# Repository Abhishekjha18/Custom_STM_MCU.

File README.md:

# **Custom Microcontroller Board with Multi-Shield Support**  

## Overview  
This project features a **custom-designed microcontroller board** with optimized **hardware interfaces and firmware**, developed using **CubeMX**. It supports **four interchangeable shields**, allowing multiple functionalities to be deployed simultaneously.  

## Features  
- **Custom PCB Design** – Developed using **KiCad** (schematics & layout available in this repository).  
- **Optimized Firmware** – Configured and fine-tuned with **CubeMX** for efficient performance.  
- **Multi-Shield Support** – Simultaneously deploy up to **four shields** with distinct functionalities.  
- **Scalable & Modular** – Easily adaptable for various embedded applications.  

## Access KiCad Files  
All **schematic and PCB design files** are available in the **KiCad_Files** directory of this repository. Clone or download them to modify or manufacture your custom board.  

1. Open **KiCad** and load the project files from the **KiCad_Files** folder.  
2. Use **CubeMX** to configure or modify firmware as needed.  
3. Flash the firmware to the microcontroller and test with your desired shields.

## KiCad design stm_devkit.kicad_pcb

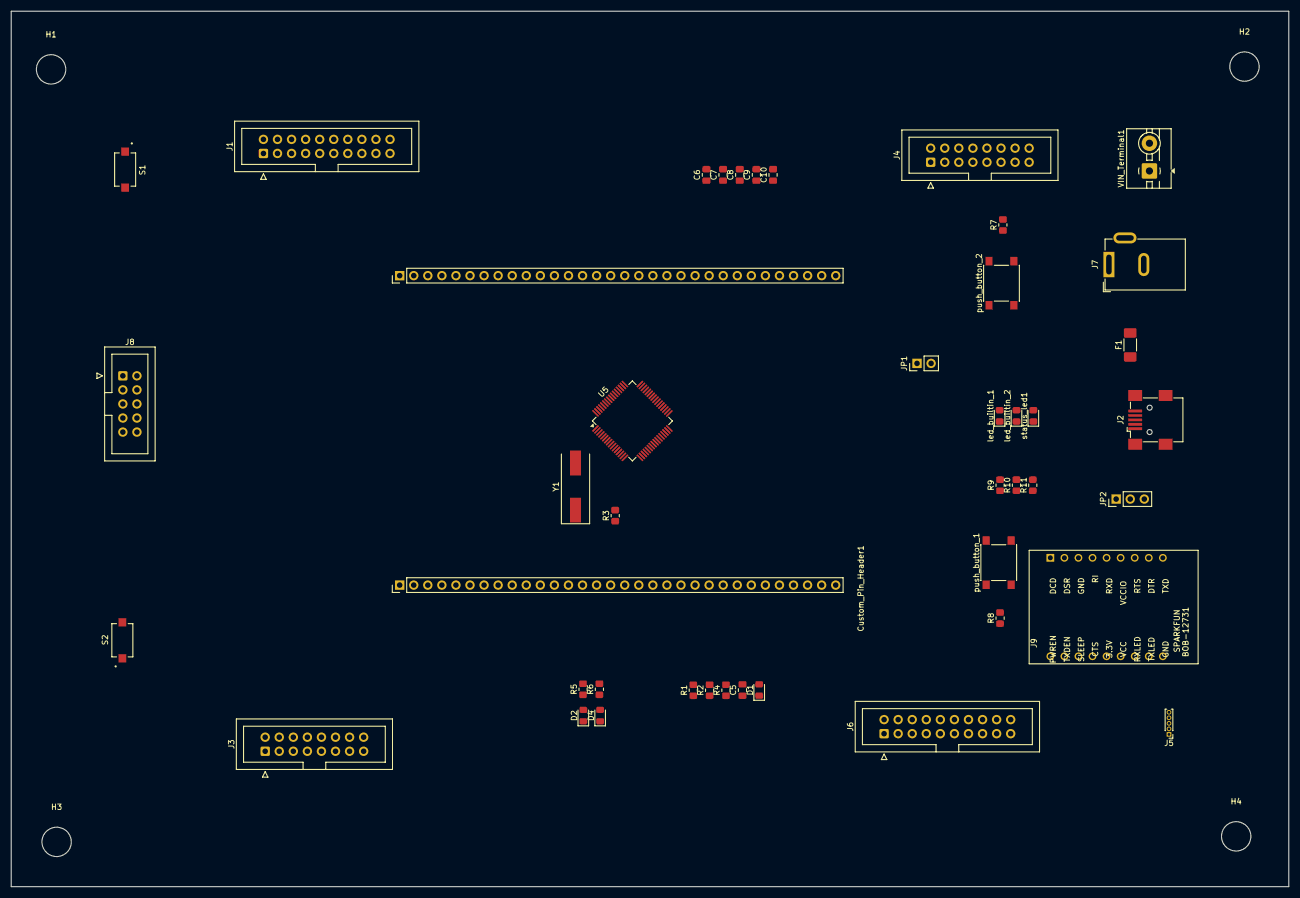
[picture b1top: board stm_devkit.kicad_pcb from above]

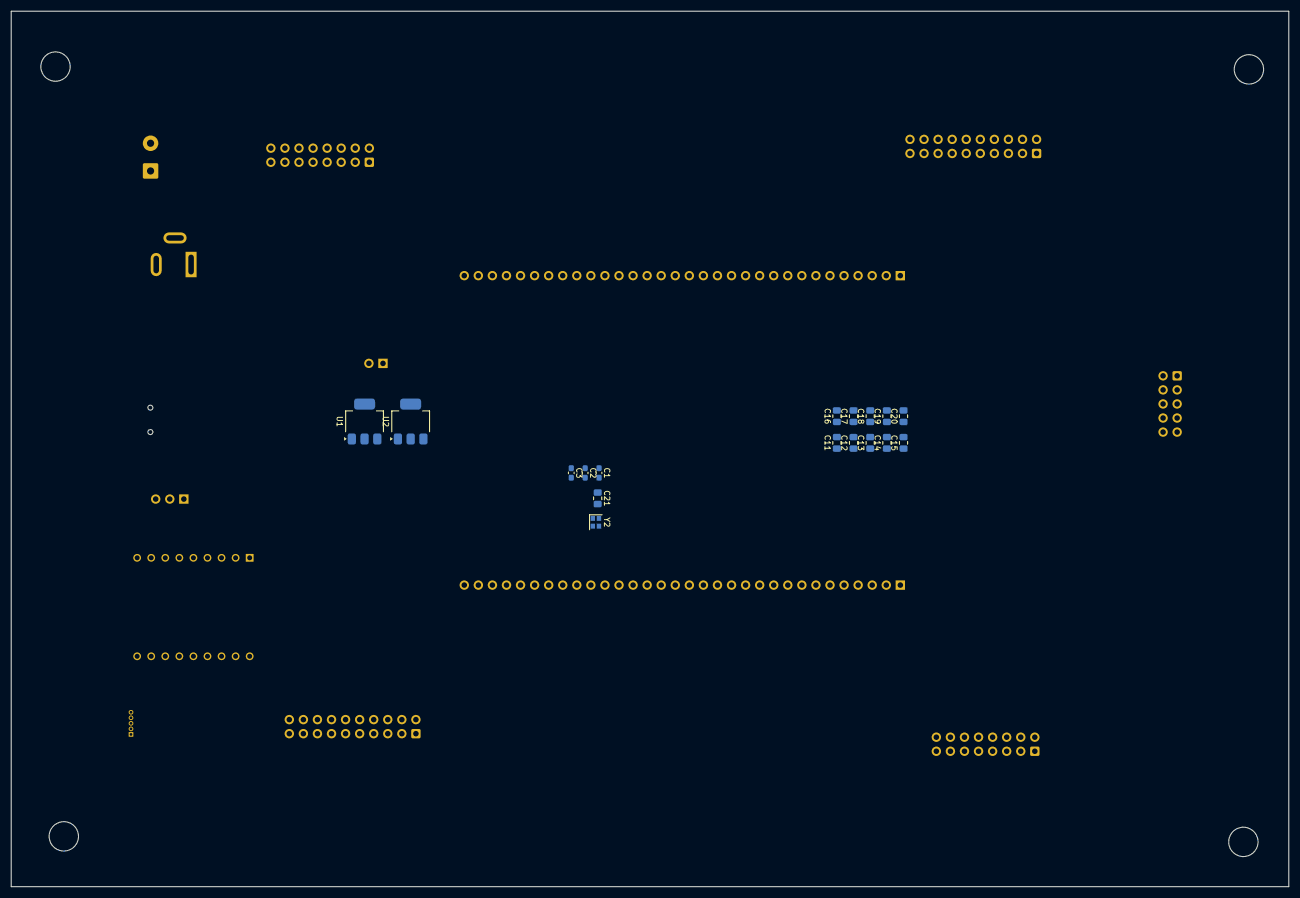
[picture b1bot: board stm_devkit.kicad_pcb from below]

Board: 2 copper layers, 230.7 x 158.1 mm, 64 parts (17 on the bottom side), 74 nets, no tracks yet.

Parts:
C1, C2: 22pF; C_0603_1608Metric_Pad1.08x0.95mm_HandSolder
C3: 10pF; C_0603_1608Metric_Pad1.08x0.95mm_HandSolder
C5: 0.01u; C_0805_2012Metric_Pad1.18x1.45mm_HandSolder
C6, C8, C9: 10uF, 25V; C_0805_2012Metric_Pad1.18x1.45mm_HandSolder
C7, C10: 1uF; C_0805_2012Metric_Pad1.18x1.45mm_HandSolder
C11, C13, C16, C19: 10uF; C_0805_2012Metric_Pad1.18x1.45mm_HandSolder
C12, C14, C15, C17, C18, C20: 0.1uF; C_0805_2012Metric_Pad1.18x1.45mm_HandSolder
C21: C_Trim; C_0805_2012Metric_Pad1.18x1.45mm_HandSolder
Custom_Pin_Header1: 64_pin_header
D1: 1N4148; D_0805_2012Metric_Pad1.15x1.40mm_HandSolder
D2: PWR_LED; LED_0805_2012Metric_Pad1.15x1.40mm_HandSolder
D4: D; D_0805_2012Metric_Pad1.15x1.40mm_HandSolder
F1: Polyfuse; C_1808_4520Metric_Pad1.72x2.30mm_HandSolder
H1, H2, H3, H4: MountingHole; MountingHole_5.3mm_M5
J1, J6: Conn_02x10_Odd_Even; IDC-Header_2x10_P2.54mm_Vertical
J2: USB_B_Mini; USB_Mini-B_Wuerth_65100516121_Horizontal
J3, J4: Conn_02x08_Odd_Even; IDC-Header_2x08_P2.54mm_Vertical
J5: Conn_01x05_Pin; PinHeader_1x05_P1.00mm_Vertical
J7: Barrel_Jack_Switch; BarrelJack_GCT_DCJ200-10-A_Horizontal
J8: Conn_02x05_Odd_Even; IDC-Header_2x05_P2.54mm_Vertical
J9: BOB-12731
JP1: Bypass; PinHeader_1x02_P2.54mm_Vertical
JP2: Jumper_3_Open; PinHeader_1x03_P2.54mm_Vertical
R1, R4, R7, R8: 10k; R_0805_2012Metric_Pad1.20x1.40mm_HandSolder
R2: 100K; R_0805_2012Metric_Pad1.20x1.40mm_HandSolder
R3: 1K; R_0805_2012Metric_Pad1.20x1.40mm_HandSolder
R5, R9, R10, R11: 1k; R_0805_2012Metric_Pad1.20x1.40mm_HandSolder
R6: 0; R_0805_2012Metric_Pad1.20x1.40mm_HandSolder
S1, S2: TS10-63-26-BE-250-SMT-TR; SW_TS10-63-26-BE-250-SMT-TR
U1: AMS1117-5.0; SOT-223-3_TabPin2
U2: AMS1117-3.3; SOT-223-3_TabPin2
U5: STM32G070RBTx; LQFP-64_10x10mm_P0.5mm
VIN_Terminal1: Screw_Terminal_01x02; TerminalBlock_MaiXu_MX126-5.0-02P_1x02_P5.00mm
Y1: 8MHz; Crystal_SMD_HC49-SD
Y2: 32.768 kHz; Crystal_SMD_2016-4Pin_2.0x1.6mm
led_builtin_1, led_builtin_2: LED; LED_0805_2012Metric_Pad1.15x1.40mm_HandSolder
push_button_1, push_button_2: SW_Push; SW_SPST_PTS645
status_led1: LED; LED_0805_2012Metric_Pad1.15x1.40mm_HandSolder

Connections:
+3.3V: C15.1, C18.1, Custom_Pin_Header1.8 (VDD), D1.1 (K), J1.13, J1.15, J5.1, J6.13, J6.15, J8.7, J8.8, J9.5 (3V3), R1.1, R4.2, R6.2, R7.1, R8.1, U5.8 (VDD)
+5V: C8.1, C13.1, C14.2, C16.1, C17.2, Custom_Pin_Header1.6 (VBAT), J1.1, J3.1, J3.3, J4.1, J4.2, J4.3, J6.1, JP1.1 (A), JP2.1 (A), U1.3 (VI), U5.6 (VBAT)
GND: C1.1, C2.1, C3.1, C5.2, C6.2, C7.2, C8.2, C9.2, C10.2, C11.2, C12.2, C13.2, C14.1, C15.2, C16.2, C17.1, C18.2, C19.2, C20.2, C21.1, Custom_Pin_Header1.7 (VREF+), Custom_Pin_Header1.9 (VSS), D2.2 (A), D4.2 (A), J1.3, J1.17, J1.19, J1.20, J2.5 (GND), J2.6 (Shield), J3.13, J3.15, J4.13, J4.15, J4.16, J5.4, J6.3, J6.17, J6.19, J6.20, J7.1, J7.3, J8.3, J8.4, J9.9 (GND), R2.2, S2.1, U1.1 (GND), U2.1 (GND), U5.7 (VREF+), U5.9 (VSS), VIN_Terminal1.2, led_builtin_1.1 (K), led_builtin_2.1 (K), push_button_1.2, push_button_2.2, status_led1.1 (K)
I2C1_A_SCL: Custom_Pin_Header1.60 (PB6), J1.14, U5.60 (PB6)
I2C1_A_SDA: Custom_Pin_Header1.61 (PB7), J1.16, U5.61 (PB7)
I2C2_A_SCL: Custom_Pin_Header1.43 (PA11), J3.14, U5.43 (PA9/PA11)
I2C2_A_SDA: Custom_Pin_Header1.44 (PA12), J3.16, U5.44 (PA10/PA12)
I2C2_B_SCL: Custom_Pin_Header1.33 (PB13), J6.14, U5.33 (PB13)
I2C2_B_SDA: Custom_Pin_Header1.34 (PB14), J6.16, U5.34 (PB14)
LED_1: Custom_Pin_Header1.35 (PB15), R9.1, U5.35 (PB15)
LED_2: Custom_Pin_Header1.40 (PD8), R10.1, U5.40 (PD8)
NRST: C5.1, Custom_Pin_Header1.12 (NRST), D1.2 (A), J8.1, R1.2, S2.2, U5.12 (NRST)
unnamed: C2.2, R3.2, Y1.1
unnamed: D2.1 (K), R5.2
unnamed: R4.1, S1.2
unnamed: C6.1, C7.1, R5.1, R6.1, U2.3 (VI)
unnamed: F1.2, J7.2, VIN_Terminal1.1
unnamed: R10.2, led_builtin_1.2 (A)
unnamed: R9.2, led_builtin_2.2 (A)
unnamed: R11.2, status_led1.2 (A)
OSC32_IN: C3.2, Custom_Pin_Header1.4 (PC14-OSC32_IN), U5.4 (PC14), Y2.2
OSC32_OUT: C21.2, Custom_Pin_Header1.5 (PC15-OSC32_OUT), U5.5 (PC15), Y2.1
OSC_IN: C1.2, U5.10 (PF0), Y1.2
OSC_OUT: R3.1, U5.11 (PF1)
PA8: Custom_Pin_Header1.36 (PA8), J4.11, U5.36 (PA8)
PC0: Custom_Pin_Header1.13 (PC0), J6.9, U5.13 (PC0)
PC1: Custom_Pin_Header1.14 (PC1), J6.11, U5.14 (PC1)
PC2: Custom_Pin_Header1.15 (PC2), J4.4, U5.15 (PC2)
PC3: Custom_Pin_Header1.16 (PC3), J4.6, U5.16 (PC3)
PC6: Custom_Pin_Header1.39 (PC7), J3.9, U5.38 (PC6)
PC7: Custom_Pin_Header1.38 (PC6), J3.11, U5.39 (PC7)
PC8: Custom_Pin_Header1.49 (PC9), J1.9, U5.48 (PC8)
PC9: Custom_Pin_Header1.48 (PC8), J1.11, U5.49 (PC9)
PD2: Custom_Pin_Header1.56 (PD6), J4.8, U5.52 (PD2)
PD5: Custom_Pin_Header1.53 (PD3), J4.10, U5.55 (PD5)
PD6: Custom_Pin_Header1.52 (PD2), J4.12, U5.56 (PD6)
PD9: Custom_Pin_Header1.41 (PD9), J4.14, U5.41 (PD9)
PUSH_DEF_1: Custom_Pin_Header1.30 (PB10), R8.2, U5.30 (PB10), push_button_1.1
PUSH_DEF_2: Custom_Pin_Header1.2 (PC12), R7.2, U5.2 (PC12), push_button_2.1
SPI1_A_MISO: Custom_Pin_Header1.24 (PA7), J6.6, U5.24 (PA7)
SPI1_A_MOSI: Custom_Pin_Header1.23 (PA6), J6.4, U5.23 (PA6)
SPI1_A_NSS: Custom_Pin_Header1.21 (PA4), J6.8, U5.21 (PA4)
SPI1_A_SCK: Custom_Pin_Header1.22 (PA5), J6.2, U5.22 (PA5)
SPI1_B_MISO: Custom_Pin_Header1.59 (PB5), J3.6, U5.59 (PB5)
SPI1_B_MOSI: Custom_Pin_Header1.58 (PB4), J3.4, U5.58 (PB4)
SPI1_B_NSS: Custom_Pin_Header1.47 (PA15), J3.8, U5.47 (PA15)
SPI1_B_SCK: Custom_Pin_Header1.57 (PB3), J3.2, U5.57 (PB3)
SPI2_B_MISO: Custom_Pin_Header1.55 (PD5), J1.6, U5.53 (PD3)
SPI2_B_MOSI: Custom_Pin_Header1.54 (PD4), J1.4, U5.54 (PD4)
SPI2_B_NSS: Custom_Pin_Header1.50 (PD0), J1.8, U5.50 (PD0)
SPI2_B_SCK: Custom_Pin_Header1.51 (PD1), J1.2, U5.51 (PD1)
STATUS_LED: Custom_Pin_Header1.3 (PC13), R11.1, U5.3 (PC13)
SWCLK/ BOOT0: Custom_Pin_Header1.46 (PA14-BOOT0), J8.6, R2.1, S1.1, U5.46 (PA14)
SWDIO: Custom_Pin_Header1.45 (PA13), J8.2, U5.45 (PA13)
USART2_A_RX: Custom_Pin_Header1.42 (PA10), J3.12, U5.42 (PA10)
USART2_A_TX: Custom_Pin_Header1.37 (PA9), J3.10, U5.37 (PA9)
USART2_B_RX: Custom_Pin_Header1.20 (PA3), J6.12, U5.20 (PA3)
USART2_B_TX: Custom_Pin_Header1.19 (PA2), J6.10, U5.19 (PA2)
USART3_A_RX_BOOT: Custom_Pin_Header1.1 (PC11), J5.3, J9.14 (RXD), U5.1 (PC11)
USART3_A_TX_BOOT: Custom_Pin_Header1.64 (PC10), J5.2, J9.10 (TXD), U5.64 (PC10)
USART3_B_RX: Custom_Pin_Header1.63 (PB9), J1.12, U5.63 (PB9)
USART3_B_TX: Custom_Pin_Header1.62 (PB8), J1.10, U5.62 (PB8)
USB_5V: J2.1 (VBUS), JP2.3 (B)
Vin: C9.1, C11.1, C12.1, C19.1, C20.1, D4.1 (K), F1.1, J1.18, J6.18, JP1.2 (B), U1.2 (VO)
reg_5v: C10.1, J5.5, J8.9, J8.10, JP2.2 (C), U2.2 (VO)
~PA0: Custom_Pin_Header1.17 (PA0), J1.5, U5.17 (PA0)
~PA1: Custom_Pin_Header1.18 (PA1), J1.7, U5.18 (PA1)
~PB0: Custom_Pin_Header1.27 (PB0), J3.7, U5.27 (PB0)
~PB1: Custom_Pin_Header1.28 (PB1), J3.5, U5.28 (PB1)
~PB2: Custom_Pin_Header1.29 (PB2), J4.5, U5.29 (PB2)
~PB11: Custom_Pin_Header1.31 (PB11), J4.7, U5.31 (PB11)
~PB12: Custom_Pin_Header1.32 (PB12), J4.9, U5.32 (PB12)
~PC4: Custom_Pin_Header1.25 (PC4), J6.5, U5.25 (PC4)
~PC5: Custom_Pin_Header1.26 (PC5), J6.7, U5.26 (PC5)
